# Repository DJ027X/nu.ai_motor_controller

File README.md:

# nu.ai_motor_controller
Designed with KiCAD 5.

You'll also want to grab my custom KiCAD library repo, otherwise parts may not load in.

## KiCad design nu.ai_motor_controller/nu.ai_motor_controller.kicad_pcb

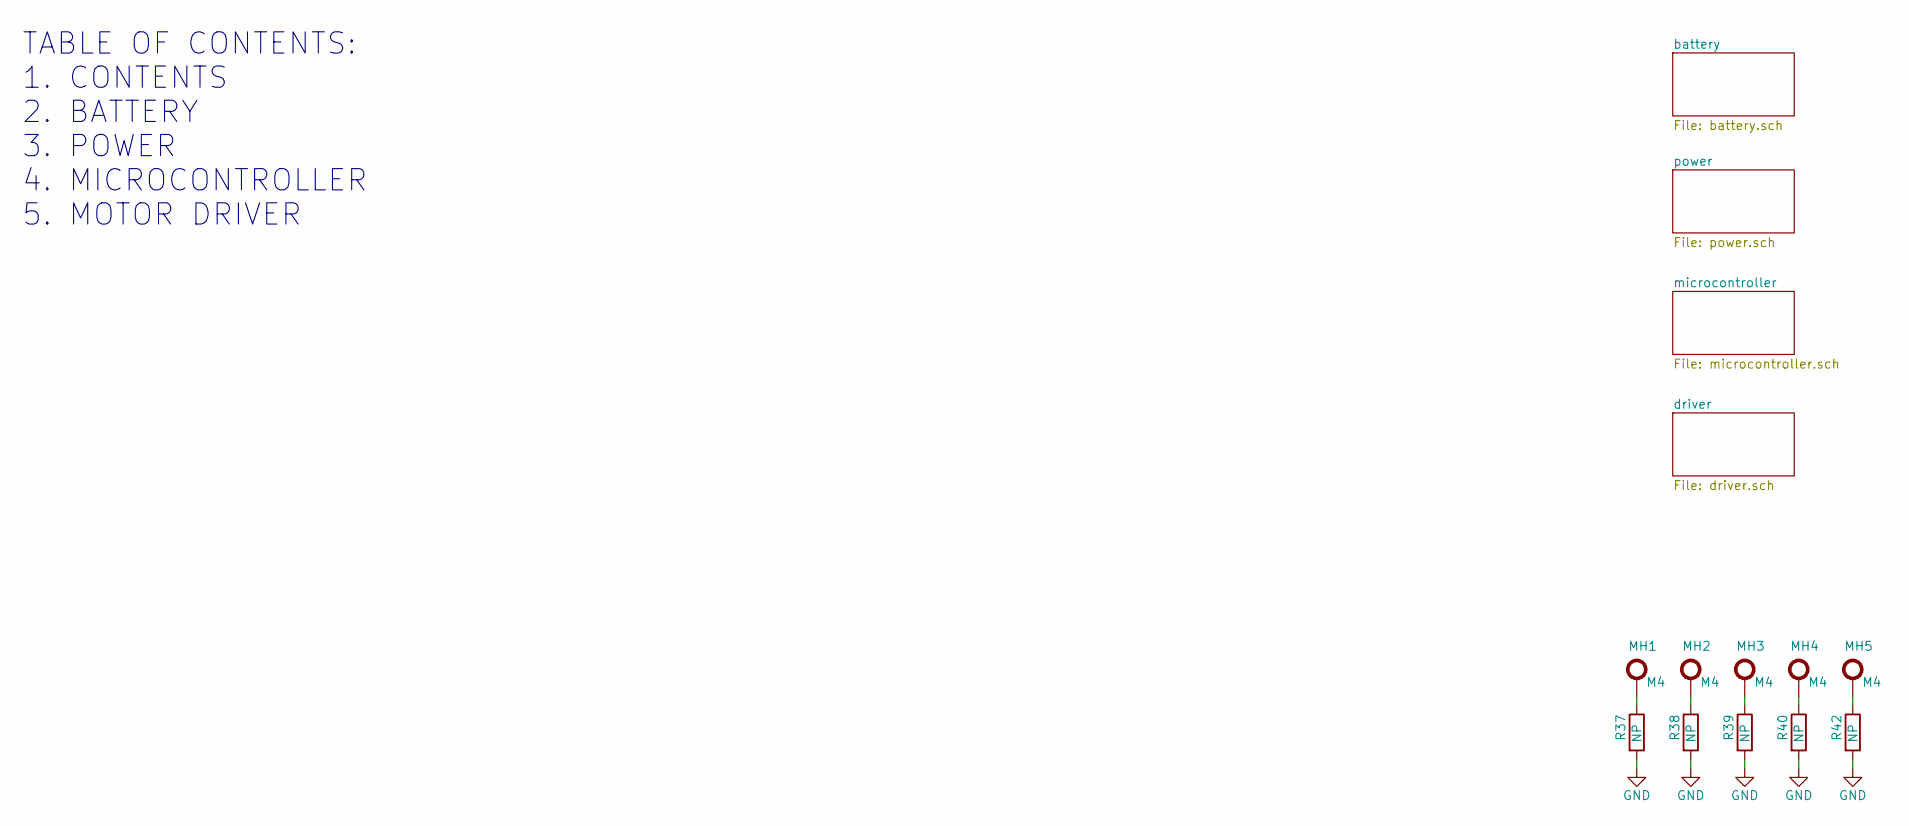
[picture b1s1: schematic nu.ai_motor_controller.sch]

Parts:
MH1, MH2, MH3, MH4, MH5: M4_MOUNTING_HOLE; MountingHole_4.3mm_M4_Pad
R37, R38, R39, R40, R42: NP_R_0603; NP_0603

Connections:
GND: R37.2, R38.2, R39.2, R40.2, R42.2; also elsewhere on the board
unnamed: MH1.1, R37.1
unnamed: MH2.1, R38.1
unnamed: MH3.1, R39.1
unnamed: MH4.1, R40.1
unnamed: MH5.1, R42.1

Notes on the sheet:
TABLE OF CONTENTS: 1. CONTENTS 2. BATTERY 3. POWER 4. MICROCONTROLLER 5. MOTOR DRIVER

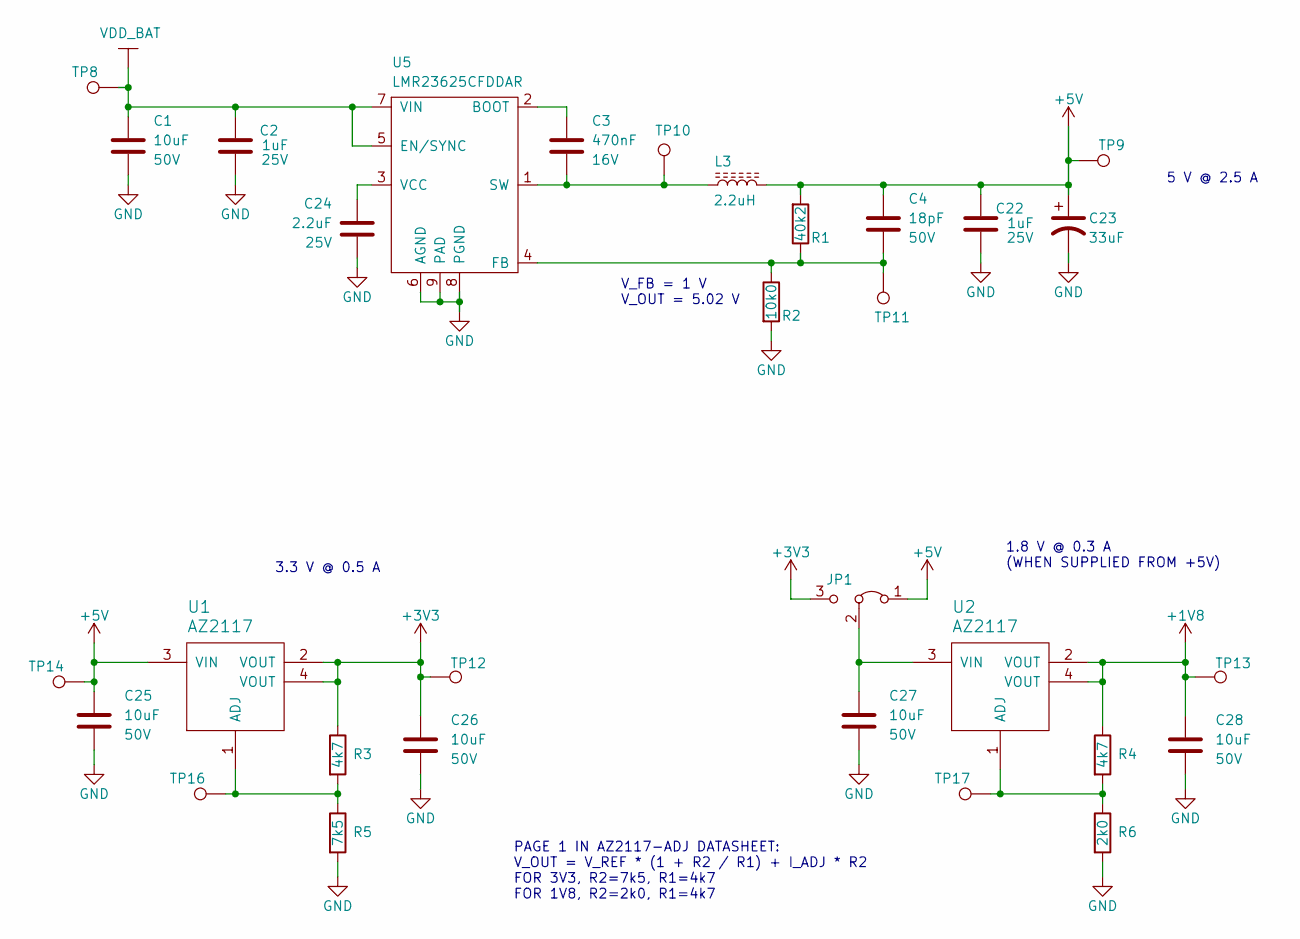
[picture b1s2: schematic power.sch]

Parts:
C1, C25, C26, C27, C28: CL10B103KB8SFNC; C_0603_1608Metric; Rating 50V
C2, C22: CL10B105KA8NNNC; C_0603_1608Metric; Rating 25V
C3: CL10B474KO8NNNC; C_0603_1608Metric; Rating 16V
C4: C0603C180K5RACAUTO; C_0603_1608Metric; Rating 50V
C23: ESH336M035AC3AA; CP_Radial_D5.0mm_P2.00mm
C24: GRM188R61E225KA12D; C_0603_1608Metric; Rating 25V
JP1: Jumper_3_Bridged12; PinHeader_1x03_P2.54mm_Vertical
L3: NR6028T2R2N; L_Taiyo-Yuden_NR-60xx
R1: RMCF0603FT40K2; R_0603_1608Metric
R2: CR0603-JW-103ELF; R_0603_1608Metric
R3, R4: RMCF0603FT4K70; R_0603_1608Metric
R5: RMCF0603FT7K50; R_0603_1608Metric
R6: RMCF0603FT2K00; R_0603_1608Metric
TP8, TP9, TP10, TP11, TP12, TP13, TP14, TP16, TP17: PTH_0.5_mm; TestPoint_THTPad_D1.0mm_Drill0.5mm
U1, U2: AZ2117; SOT-223
U5: LMR23625CFDDAR; 8-PowerSOIC

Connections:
+1V8: C28.1, R4.1, TP13.1, U2.2 (VOUT), U2.4 (VOUT); also elsewhere on the board
+3V3: C26.1, JP1.3 (B), R3.1, TP12.1, U1.2 (VOUT), U1.4 (VOUT); also elsewhere on the board
+5V: C4.1, C22.1, C23.1, C25.1, JP1.1 (A), L3.2, R1.1, TP9.1, TP14.1, U1.3 (VIN); also elsewhere on the board
GND: C1.2, C2.2, C22.2, C23.2, C24.2, C25.2, C26.2, C27.2, C28.2, R2.2, R5.2, R6.2, U5.6 (AGND), U5.8 (PGND), U5.9 (PAD); also elsewhere on the board
unnamed: C3.1, U5.2 (BOOT)
unnamed: C3.2, L3.1, TP10.1, U5.1 (SW)
unnamed: C4.2, R1.2, R2.1, TP11.1, U5.4 (FB)
unnamed: C24.1, U5.3 (VCC)
unnamed: C27.1, JP1.2 (C), U2.3 (VIN)
unnamed: R3.2, R5.1, TP16.1, U1.1 (ADJ)
unnamed: R4.2, R6.1, TP17.1, U2.1 (ADJ)
VDD_BAT: C1.1, C2.1, TP8.1, U5.5 (EN/SYNC), U5.7 (VIN); also elsewhere on the board

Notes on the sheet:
V_FB = 1 V V_OUT = 5.02 V
5 V @ 2.5 A
PAGE 1 IN AZ2117-ADJ DATASHEET: V_OUT = V_REF * (1 + R2 / R1) + I_ADJ * R2 FOR 3V3, R2=7k5, R1=4k7 FOR 1V8, R2=2k0, R1=4k7
3.3 V @ 0.5 A
1.8 V @ 0.3 A (WHEN SUPPLIED FROM +5V)

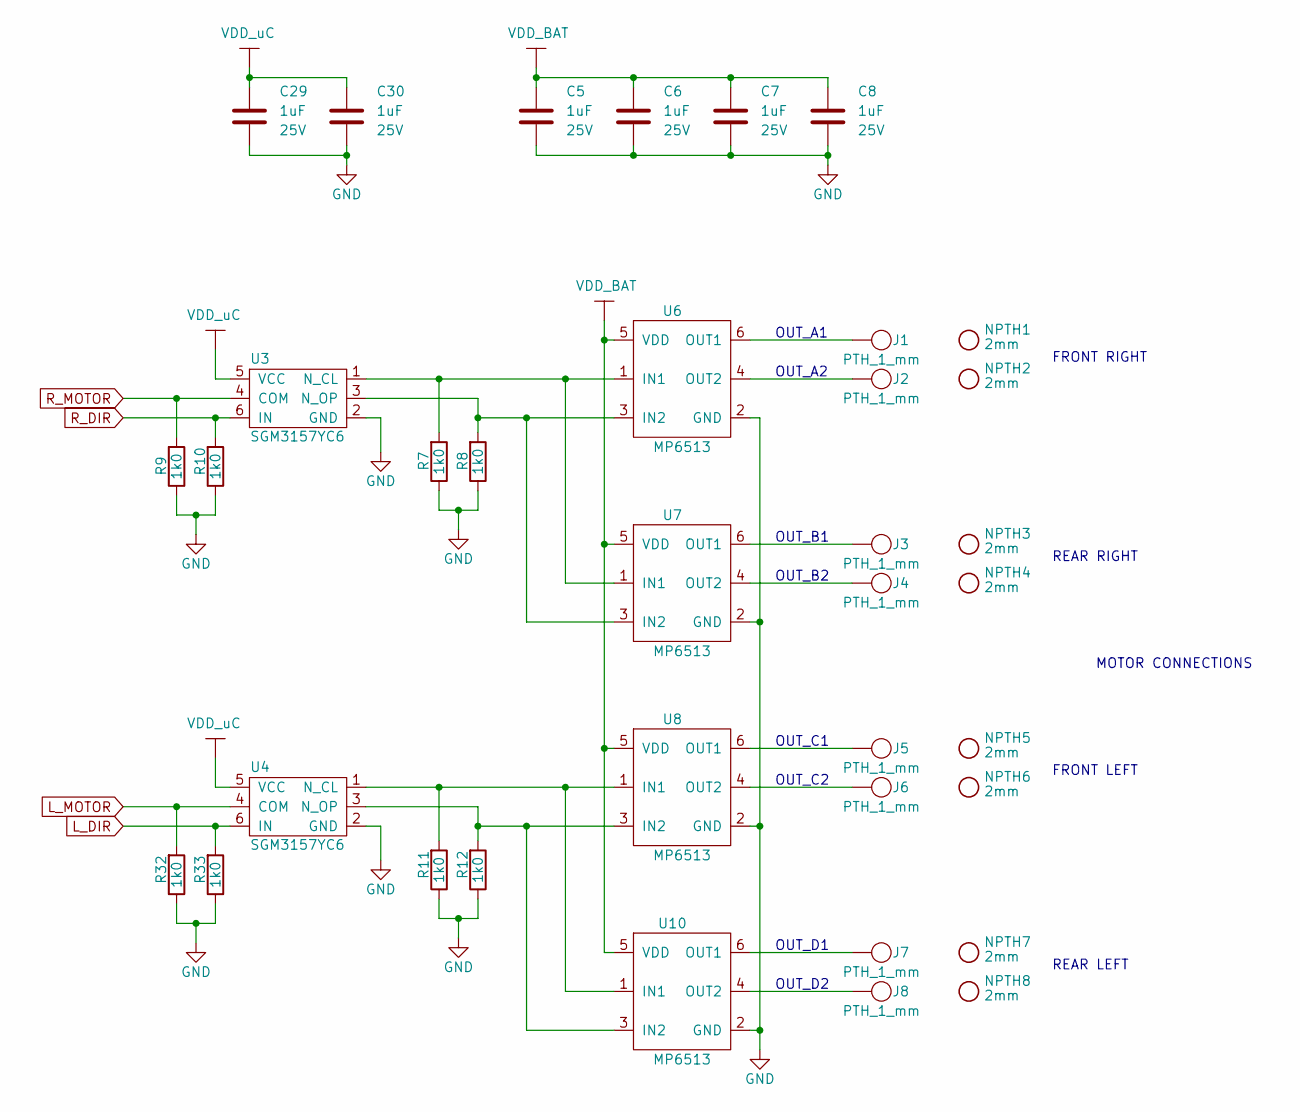
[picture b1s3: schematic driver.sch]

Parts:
C5, C6, C7, C8, C29, C30: CL10B105KA8NNNC; C_0603_1608Metric; Rating 25V
J1, J2, J3, J4, J5, J6, J7, J8: PTH_1_mm; TestPoint_THTPad_D2.0mm_Drill1.0mm
NPTH1, NPTH2, NPTH3, NPTH4, NPTH5, NPTH6, NPTH7, NPTH8: NPTH_2mm
R7, R8, R9, R10, R11, R12, R32, R33: RC0603JR-071KL; R_0603_1608Metric
U3, U4: SGM3157YC6; SOT-363_SC-70-6
U6, U7, U8, U10: MP6513; TSOT23-6

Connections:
GND: C5.2, C6.2, C7.2, C8.2, C29.2, C30.2, R7.2, R8.2, R9.2, R10.2, R11.2, R12.2, R32.2, R33.2, U3.2 (GND), U4.2 (GND), U6.2 (GND), U7.2 (GND), U8.2 (GND), U10.2 (GND); also elsewhere on the board
L_DIR: R33.1, U4.6 (IN); also elsewhere on the board
L_MOTOR: R32.1, U4.4 (COM); also elsewhere on the board
unnamed: J1.1, U6.6 (OUT1)
unnamed: J2.1, U6.4 (OUT2)
unnamed: J3.1, U7.6 (OUT1)
unnamed: J4.1, U7.4 (OUT2)
unnamed: J5.1, U8.6 (OUT1)
unnamed: J6.1, U8.4 (OUT2)
unnamed: J7.1, U10.6 (OUT1)
unnamed: J8.1, U10.4 (OUT2)
unnamed: R7.1, U3.1 (N_CL), U6.1 (IN1), U7.1 (IN1)
unnamed: R8.1, U3.3 (N_OP), U6.3 (IN2), U7.3 (IN2)
unnamed: R11.1, U4.1 (N_CL), U8.1 (IN1), U10.1 (IN1)
unnamed: R12.1, U4.3 (N_OP), U8.3 (IN2), U10.3 (IN2)
R_DIR: R10.1, U3.6 (IN); also elsewhere on the board
R_MOTOR: R9.1, U3.4 (COM); also elsewhere on the board
VDD_BAT: C5.1, C6.1, C7.1, C8.1, U6.5 (VDD), U7.5 (VDD), U8.5 (VDD), U10.5 (VDD); also elsewhere on the board
VDD_uC: C29.1, C30.1, U3.5 (VCC), U4.5 (VCC); also elsewhere on the board

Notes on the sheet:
OUT_A1
OUT_A2
OUT_B1
OUT_B2
OUT_C1
OUT_C2
OUT_D1
OUT_D2
MOTOR CONNECTIONS
FRONT RIGHT
REAR RIGHT
FRONT LEFT
REAR LEFT

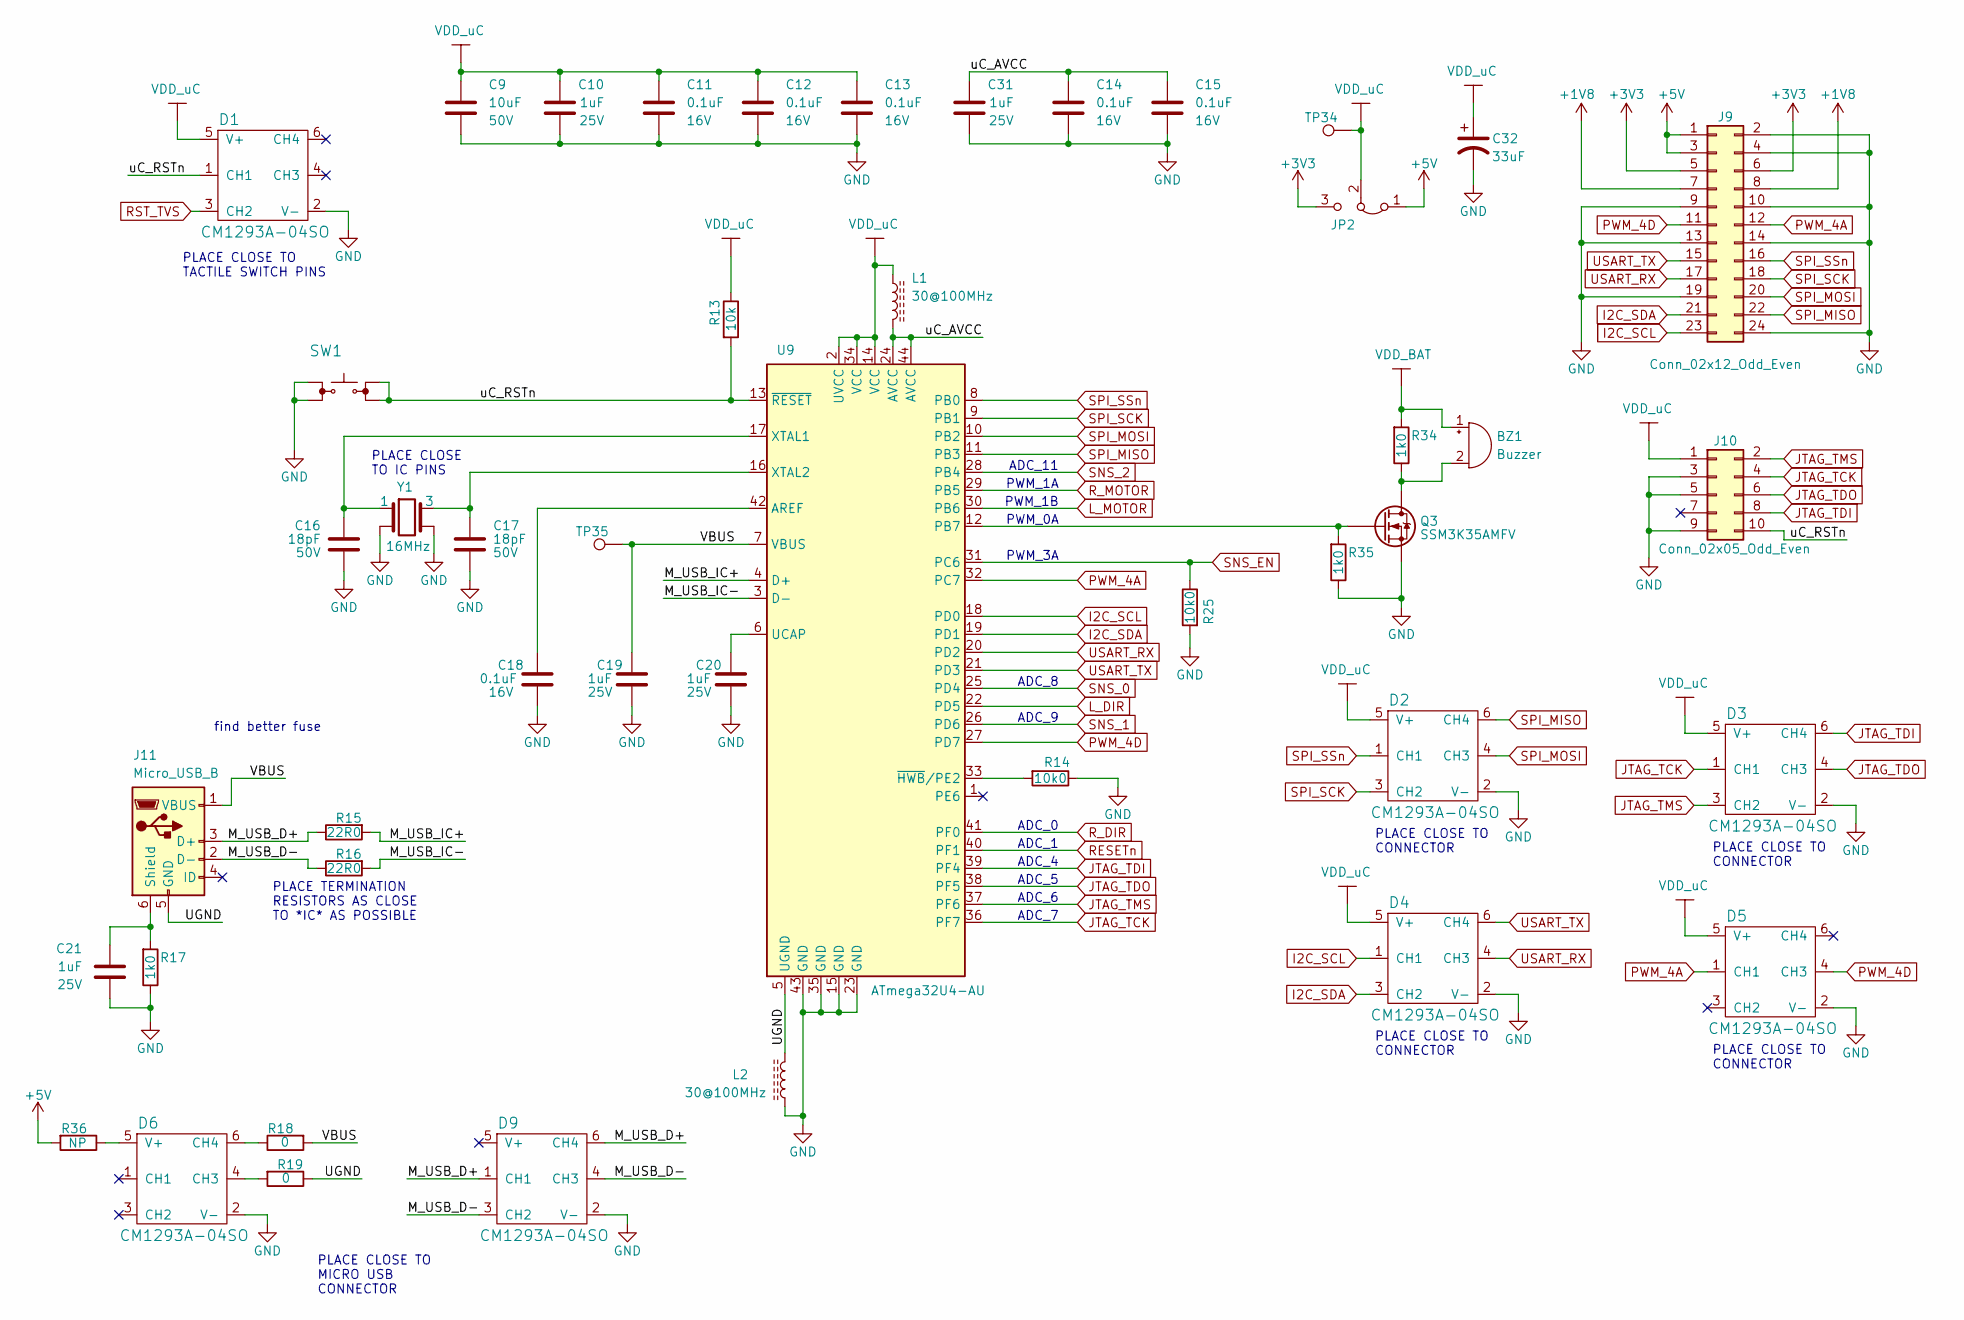
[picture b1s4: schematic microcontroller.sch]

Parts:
BZ1: Buzzer; 0.5_IN_BUZZER
C9: CL10B103KB8SFNC; C_0603_1608Metric; Rating 50V
C10, C19, C20, C21, C31: CL10B105KA8NNNC; C_0603_1608Metric; Rating 25V
C11, C12, C13, C14, C15, C18: CL10B104KO8NNNC; C_0603_1608Metric; Rating 16V
C16, C17: C0603C180K5RACAUTO; C_0603_1608Metric; Rating 50V
C32: ESH336M035AC3AA; CP_Radial_D5.0mm_P2.00mm
D1, D2, D3, D4, D5, D6, D9: CM1293A-04SO; SOT-457
J9: Conn_02x12_Odd_Even; PinHeader_2x12_P2.54mm_Vertical
J10: Conn_02x05_Odd_Even; PinHeader_2x05_P2.54mm_Vertical
J11: DX4R105JJCR1800; DX4R105JJCR1800‎_MICRO_USB_B_CONNECTOR
JP2: Jumper_3_Bridged12; PinHeader_1x03_P2.54mm_Vertical
L1, L2: CIS10P300AC; L_0603_1608Metric
Q3: SSM3K35AMFV; SOT-723
R13, R14, R25: CR0603-JW-103ELF; R_0603_1608Metric
R15, R16: RMCF0603FT22R0; R_0603_1608Metric
R17, R34, R35: RC0603JR-071KL; R_0603_1608Metric
R18, R19: RC0603JR-070RL; R_0603_1608Metric
R36: NP_R_0603; NP_0603
SW1: TACTILE_SWITCH
TP34, TP35: PTH_0.5_mm; TestPoint_THTPad_D1.0mm_Drill0.5mm
U9: ATmega32U4-AU; TQFP-44_10x10mm_P0.8mm
Y1: 7M-16.000MAAE-T; Crystal_SMD_3225-4Pin_3.2x2.5mm

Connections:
+1V8: J9.7, J9.8; also elsewhere on the board
+3V3: J9.5, J9.6, JP2.3 (B); also elsewhere on the board
+5V: J9.1, J9.3, JP2.1 (A), R36.2; also elsewhere on the board
/microcontroller/M_USB_D+: D9.1 (CH1), D9.6 (CH4), J11.3 (D+), R15.2
/microcontroller/M_USB_D-: D9.3 (CH2), D9.4 (CH3), J11.2 (D-), R16.2
/microcontroller/M_USB_IC+: R15.1, U9.4 (D+)
/microcontroller/M_USB_IC-: R16.1, U9.3 (D-)
/microcontroller/UGND: J11.5 (GND), L2.1, R19.1, U9.5 (UGND)
/microcontroller/VBUS: C19.1, J11.1 (VBUS), R18.2, TP35.1, U9.7 (VBUS)
/microcontroller/uC_AVCC: C14.1, C15.1, C31.1, L1.2, U9.24 (AVCC), U9.44 (AVCC)
/microcontroller/uC_RSTn: D1.1 (CH1), J10.10, R13.2, SW1.2, U9.13 (~RESET)
GND: C9.2, C10.2, C11.2, C12.2, C13.2, C14.2, C15.2, C16.2, C17.2, C18.2, C19.2, C20.2, C21.2, C31.2, C32.2, D1.2 (V-), D2.2 (V-), D3.2 (V-), D4.2 (V-), D5.2 (V-), D6.2 (V-), D9.2 (V-), J9.2, J9.4, J9.9, J9.10, J9.13, J9.14, J9.19, J9.24, J10.3, J10.5, J10.9, L2.2, Q3.2 (S), R14.1, R17.2, R25.2, R35.2, SW1.1, U9.15 (GND), U9.23 (GND), U9.35 (GND), U9.43 (GND), Y1.2, Y1.4; also elsewhere on the board
I2C_SCL: D4.1 (CH1), J9.23, U9.18 (PD0)
I2C_SDA: D4.3 (CH2), J9.21, U9.19 (PD1)
JTAG_TCK: D3.1 (CH1), J10.4, U9.36 (PF7)
JTAG_TDI: D3.6 (CH4), J10.8, U9.39 (PF4)
JTAG_TDO: D3.4 (CH3), J10.6, U9.38 (PF5)
JTAG_TMS: D3.3 (CH2), J10.2, U9.37 (PF6)
L_DIR: U9.22 (PD5); also elsewhere on the board
L_MOTOR: U9.30 (PB6); also elsewhere on the board
unnamed: BZ1.2 (+), Q3.3 (D), R34.2
unnamed: C16.1, U9.17 (XTAL1), Y1.1
unnamed: C17.1, U9.16 (XTAL2), Y1.3
unnamed: C18.1, U9.42 (AREF)
unnamed: C20.1, U9.6 (UCAP)
unnamed: C21.1, J11.6 (Shield), R17.1
unnamed: D6.4 (CH3), R19.2
unnamed: D6.5 (V+), R36.1
unnamed: D6.6 (CH4), R18.1
unnamed: Q3.1 (G), R35.1, U9.12 (PB7)
unnamed: R14.2, U9.33 (~HWB~/PE2)
PWM_4A: D5.1 (CH1), J9.12, U9.32 (PC7)
PWM_4D: D5.4 (CH3), J9.11, U9.27 (PD7)
RESETn: U9.40 (PF1); also elsewhere on the board
RST_TVS: D1.3 (CH2); also elsewhere on the board
R_DIR: U9.41 (PF0); also elsewhere on the board
R_MOTOR: U9.29 (PB5); also elsewhere on the board
SNS_0: U9.25 (PD4); also elsewhere on the board
SNS_1: U9.26 (PD6); also elsewhere on the board
SNS_2: U9.28 (PB4); also elsewhere on the board
SNS_EN: R25.1, U9.31 (PC6); also elsewhere on the board
SPI_MISO: D2.6 (CH4), J9.22, U9.11 (PB3)
SPI_MOSI: D2.4 (CH3), J9.20, U9.10 (PB2)
SPI_SCK: D2.3 (CH2), J9.18, U9.9 (PB1)
SPI_SSn: D2.1 (CH1), J9.16, U9.8 (PB0)
USART_RX: D4.4 (CH3), J9.17, U9.20 (PD2)
USART_TX: D4.6 (CH4), J9.15, U9.21 (PD3)
VDD_BAT: BZ1.1 (-), R34.1; also elsewhere on the board
VDD_uC: C9.1, C10.1, C11.1, C12.1, C13.1, C32.1, D1.5 (V+), D2.5 (V+), D3.5 (V+), D4.5 (V+), D5.5 (V+), J10.1, JP2.2 (C), L1.1, R13.1, TP34.1, U9.2 (UVCC), U9.14 (VCC), U9.34 (VCC); also elsewhere on the board

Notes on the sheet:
PLACE TERMINATION RESISTORS AS CLOSE TO *IC* AS POSSIBLE
PLACE CLOSE TO MICRO USB CONNECTOR
PLACE CLOSE TO IC PINS
ADC_11
PWM_1A
PWM_1B
ADC_8
ADC_9
ADC_0
ADC_1
ADC_4
ADC_5
ADC_6
ADC_7
PLACE CLOSE TO TACTILE SWITCH PINS
PWM_0A
PLACE CLOSE TO CONNECTOR
find better fuse
PWM_3A

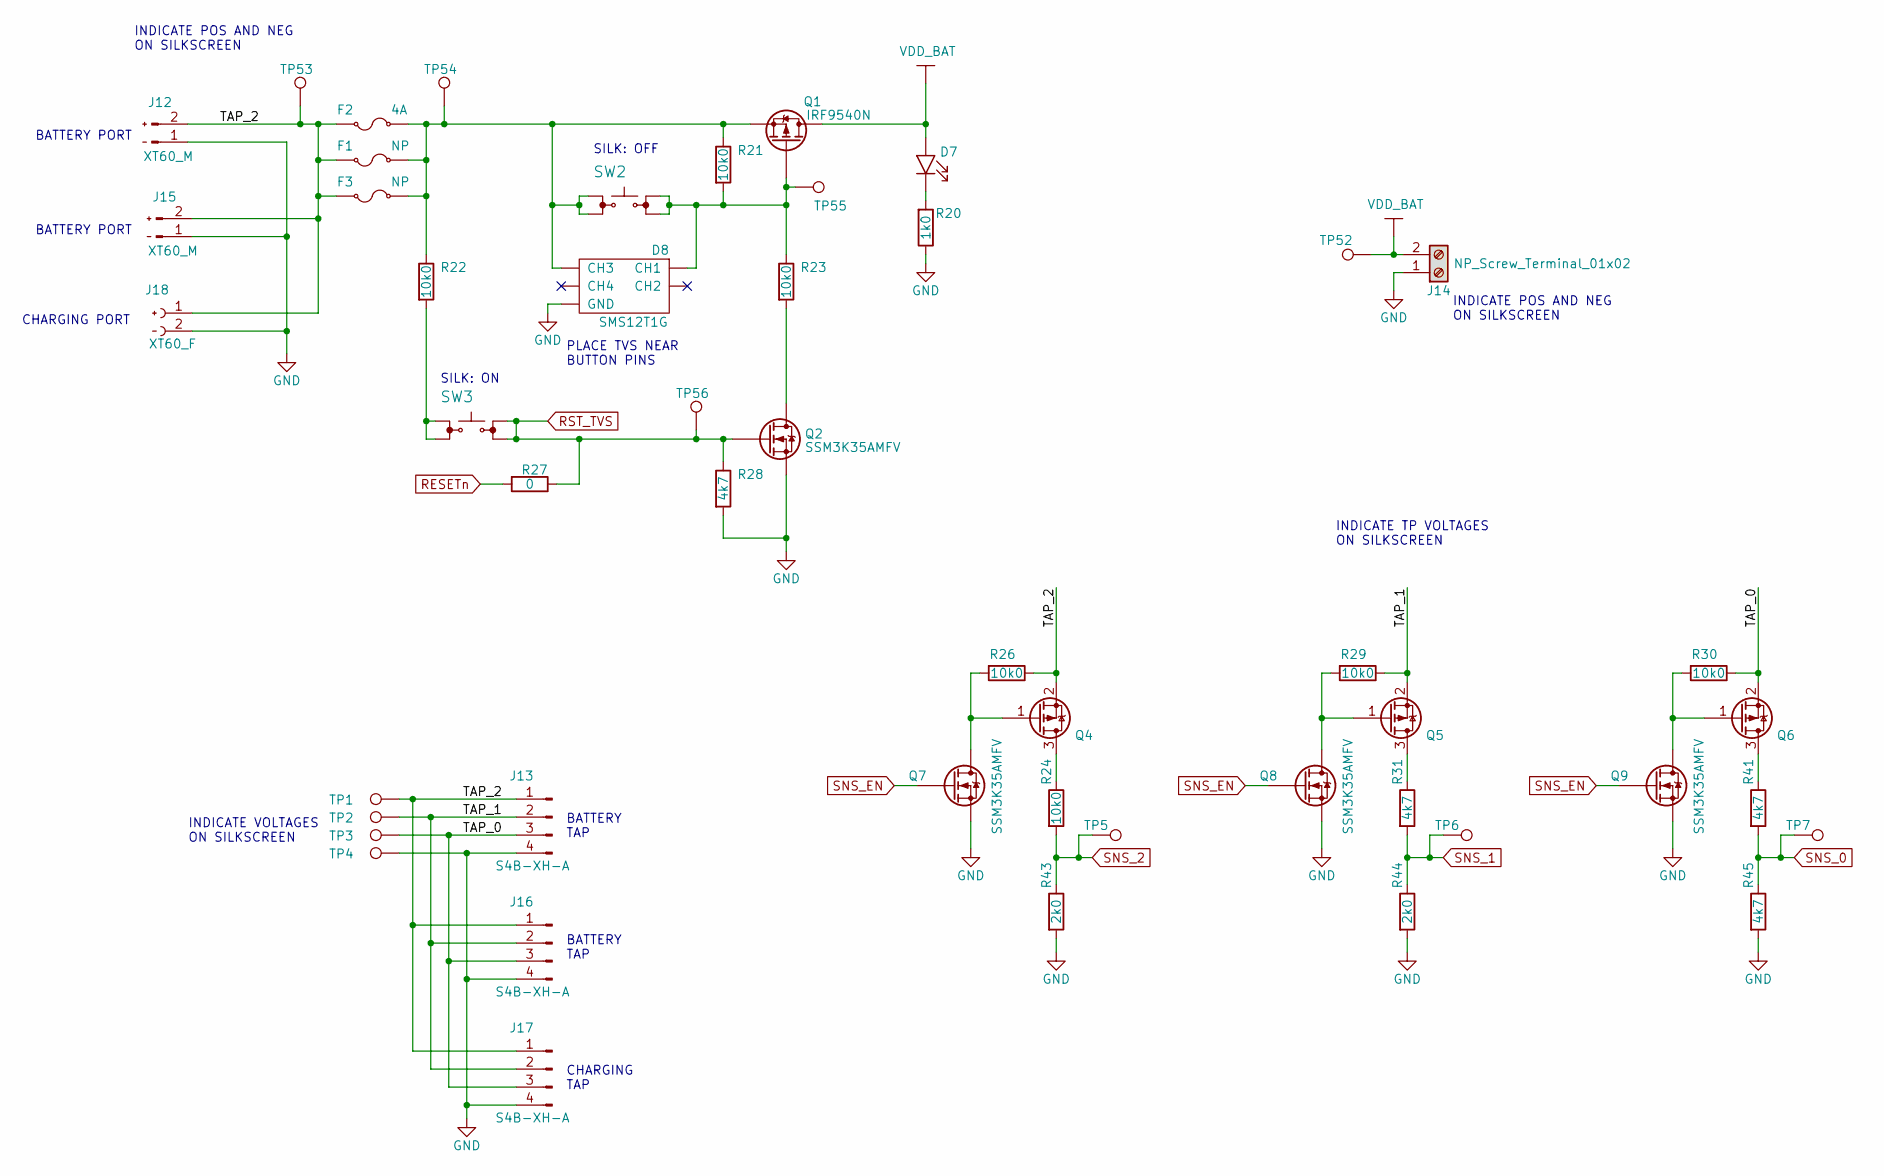
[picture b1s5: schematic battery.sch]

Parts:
D7: LED_GENERIC_0805; D_0805_2012Metric
D8: SMS12T1G; SOT-457
F1, F3: NP_FUSE_0603; Fuse_0603_1608Metric
F2: ERB-RE4R00V; Fuse_0603_1608Metric; rating 4A
J12, J15: XT60_RA_MALE; XT60PW
J13, J16, J17: S4B-XH-A; X4B-XH-A
J14: NP_Screw_Terminal_01x02; TERMINAL_BLOCK_1x2
J18: XT60_RA_FEMALE; XT60PW
Q1: IRF9540N; TO-220-3_Horizontal_TabDown
Q2, Q7, Q8, Q9: SSM3K35AMFV; SOT-723
Q4, Q5, Q6: AO3407A; SOT-23
R20: RC0603JR-071KL; R_0603_1608Metric
R21, R22, R23, R24, R26, R29, R30: CR0603-JW-103ELF; R_0603_1608Metric
R27: RC0603JR-070RL; R_0603_1608Metric
R28, R31, R41, R45: RMCF0603FT4K70; R_0603_1608Metric
R43, R44: RMCF0603FT2K00; R_0603_1608Metric
SW2, SW3: TACTILE_SWITCH
TP1, TP2, TP3, TP4, TP5, TP6, TP7, TP52, TP53, TP54, TP55, TP56: PTH_0.5_mm; TestPoint_THTPad_D1.0mm_Drill0.5mm

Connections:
/battery/TAP_0: J13.3, J16.3, J17.3, Q6.2 (S), R30.1, TP3.1
/battery/TAP_1: J13.2, J16.2, J17.2, Q5.2 (S), R29.1, TP2.1
/battery/TAP_2: F1.1, F2.1, F3.1, J12.2, J13.1, J15.2, J16.1, J17.1, J18.1, Q4.2 (S), R26.1, TP1.1, TP53.1
GND: D8.2 (GND), D8.5 (GND), J12.1, J13.4, J14.1, J15.1, J16.4, J17.4, J18.2, Q2.2 (S), Q7.2 (S), Q8.2 (S), Q9.2 (S), R20.2, R28.2, R43.2, R44.2, R45.2, TP4.1; also elsewhere on the board
unnamed: D7.1 (K), R20.1
unnamed: D8.1 (CH1), Q1.1 (G), R21.2, R23.1, SW2.2, TP55.1
unnamed: D8.6 (CH3), F1.2, F2.2, F3.2, Q1.3 (S), R21.1, R22.1, SW2.1, TP54.1
unnamed: Q2.3 (D), R23.2
unnamed: Q4.1 (G), Q7.3 (D), R26.2
unnamed: Q4.3 (D), R24.1
unnamed: Q5.1 (G), Q8.3 (D), R29.2
unnamed: Q5.3 (D), R31.1
unnamed: Q6.1 (G), Q9.3 (D), R30.2
unnamed: Q6.3 (D), R41.1
unnamed: R22.2, SW3.1
RESETn: R27.2; also elsewhere on the board
RST_TVS: Q2.1 (G), R27.1, R28.1, SW3.2, TP56.1; also elsewhere on the board
SNS_0: R41.2, R45.1, TP7.1; also elsewhere on the board
SNS_1: R31.2, R44.1, TP6.1; also elsewhere on the board
SNS_2: R24.2, R43.1, TP5.1; also elsewhere on the board
SNS_EN: Q7.1 (G), Q8.1 (G), Q9.1 (G); also elsewhere on the board
VDD_BAT: D7.2 (A), J14.2, Q1.2 (D), Q1.4 (D), TP52.1; also elsewhere on the board

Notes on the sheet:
BATTERY TAP
INDICATE POS AND NEG ON SILKSCREEN
INDICATE VOLTAGES ON SILKSCREEN
PLACE TVS NEAR BUTTON PINS
SILK: OFF
SILK: ON
BATTERY PORT
CHARGING PORT
CHARGING TAP
INDICATE TP VOLTAGES ON SILKSCREEN

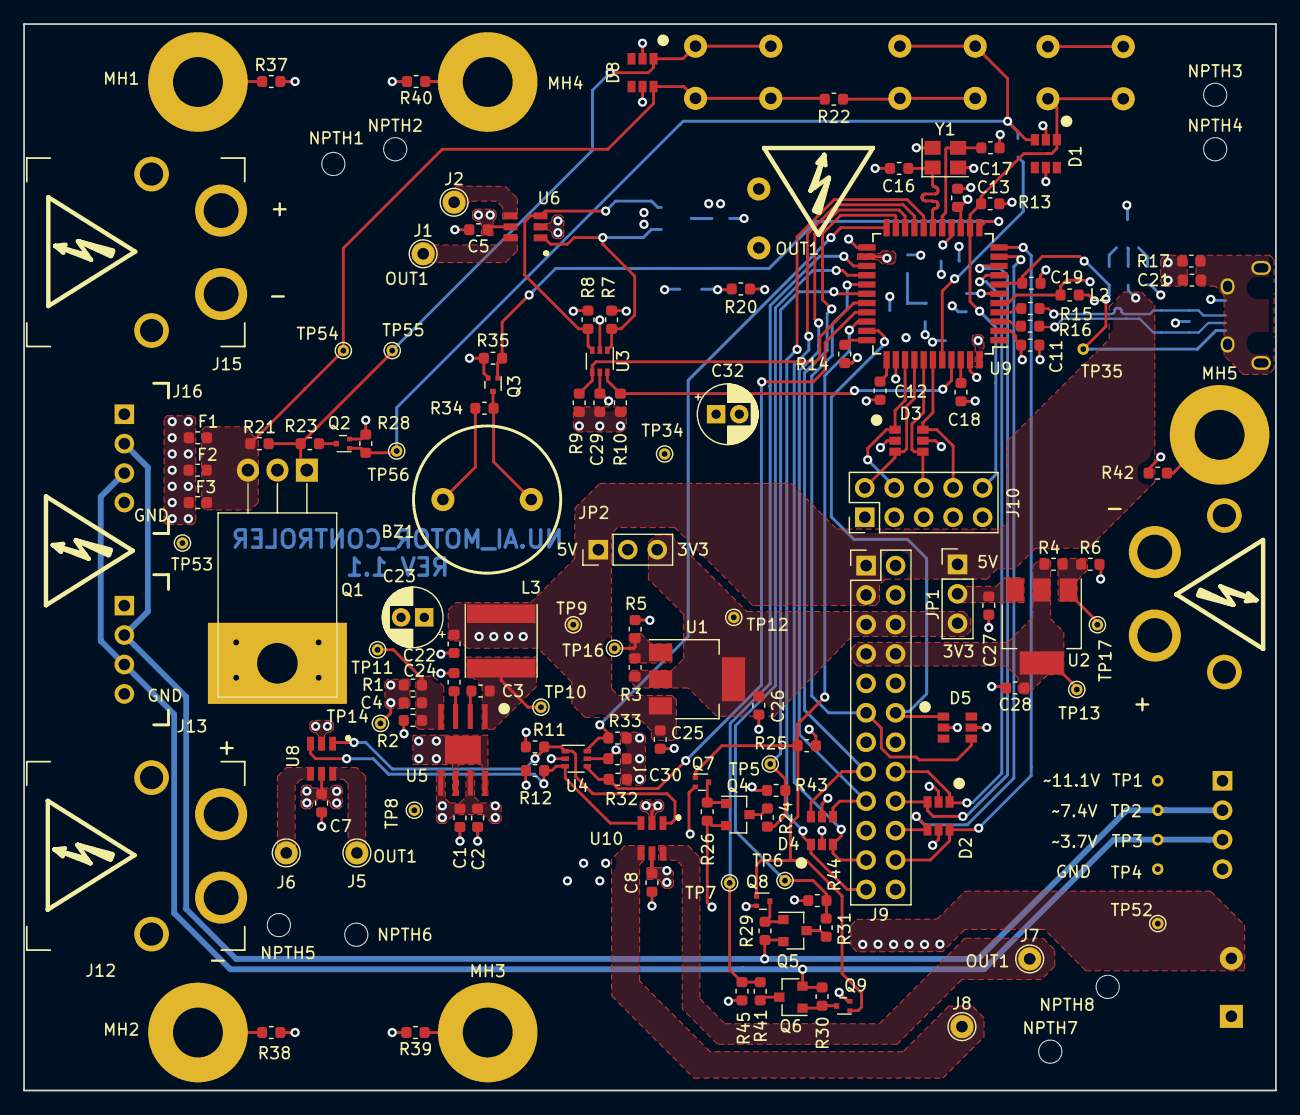
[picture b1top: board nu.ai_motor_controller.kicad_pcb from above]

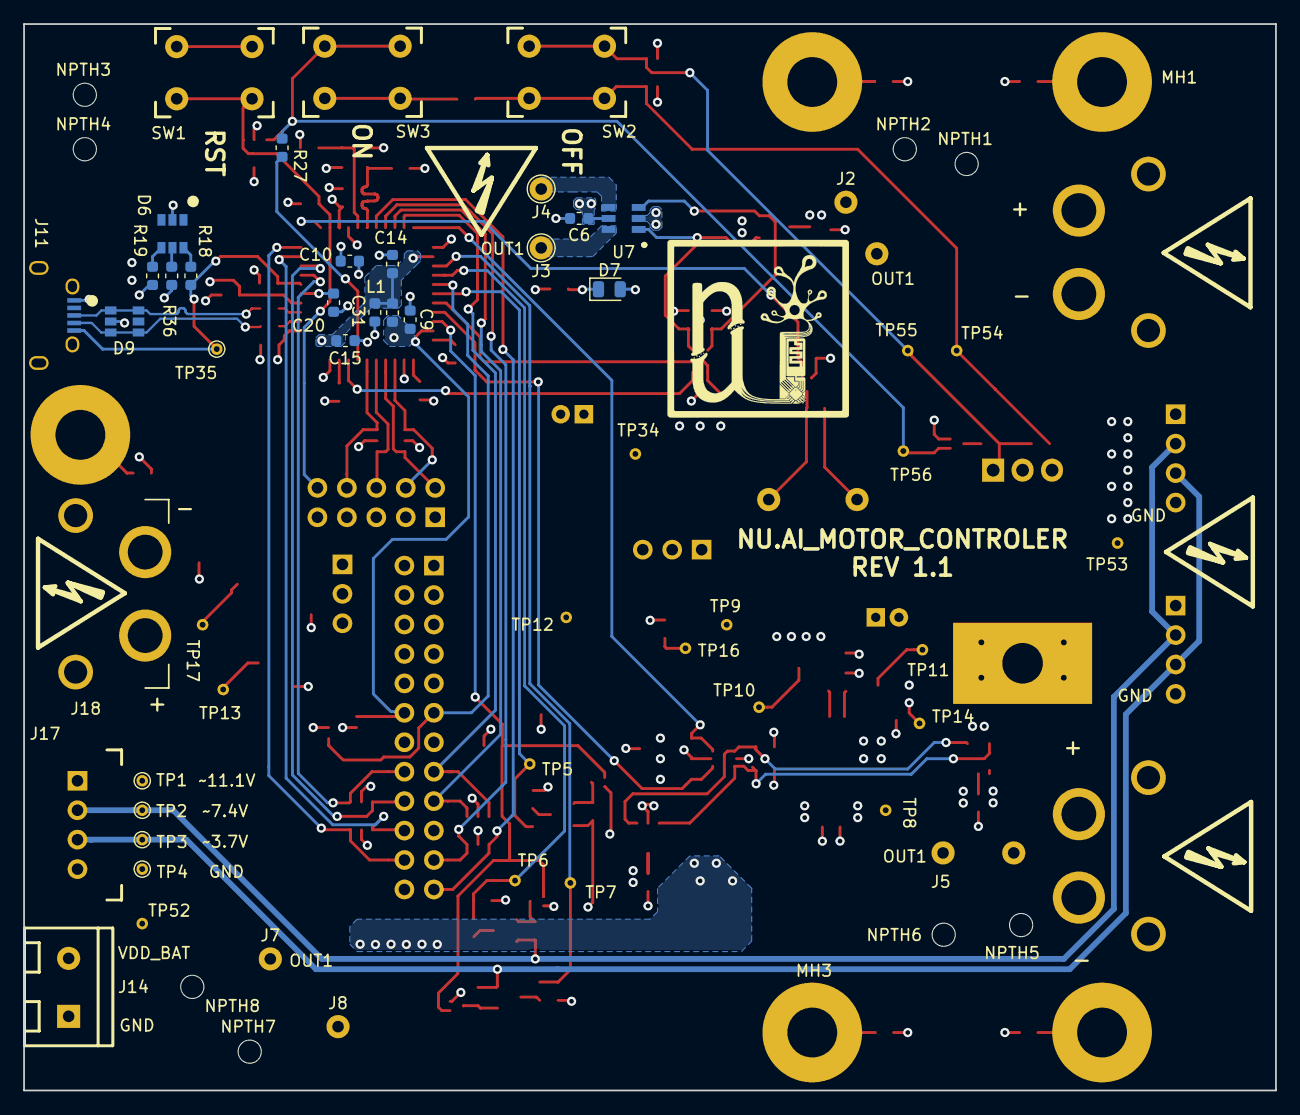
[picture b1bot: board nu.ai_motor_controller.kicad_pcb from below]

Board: 4 copper layers, 108.0 x 92.0 mm, 172 parts (30 on the bottom side), 87 nets.

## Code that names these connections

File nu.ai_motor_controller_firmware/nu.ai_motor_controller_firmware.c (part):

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
// Just some pin name mapping for your own reference
/*
PIN8  PORTB0 SPI_SSn
PIN9  PORTB1 SPI_SCK
PIN10 PORTB2 SPI_MOSI
PIN11 PORTB3 SPI_MISO
PIN28 PORTB4 SNS_2
PIN29 PORTB5 R_MOTOR
PIN30 PORTB6 L_MOTOR
PIN12 PORTB7 BUZZER
PIN31 PORTC6 SNS_EN
PIN32 PORTC7 PWM_4A
PIN18 PORTD0 I2C_SCL
PIN19 PORTD1 I2C_SDA
PIN20 PORTD2 USART_RX
PIN21 PORTD3 USART_TX
PIN25 PORTD4 SNS_0
PIN22 PORTD5 L_DIR
PIN26 PORTD6 SNS_1
PIN27 PORTD7 PWM_4D
PIN33 PORTE2 HWBn
PIN1  PORTE6 NC
PIN41 PORTF0 R_DIR
PIN40 PORTF1 RESETn
PIN39 PORTF4 JTAG_TDI
PIN38 PORTF5 JTAG_TDO
PIN37 PORTF6 JTAG_TMS
PIN36 PORTF7 JTAG_TCK
*/

// Some handy defines
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
	/*TODO: maybe set ADTS and ADATE to make conversion happen periodically. This is a power saving measure.\
	      if there aren't enough timers, just leave in free-running mode.\
	      Note however that there's a SNS_EN pin that should take care of power saving\
	      so it's probably fine free-running the ADCs.

	TODO: remember later on to make code to switch which ADC port is being read by changing MUX5..0*/
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	// Set prescalar to 256 (~122 Hz to  31250 Hz)
	TCCR0B |= 0x04;

	// Set PB7 as an output to turn the beeping on.
	// Set as input to turn off beeping.
	

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	// Set prescalar to 1024.
	TCCR3B |= 0x05;

	// Set the SNS_EN pin as an output.
	DDRC |= SNS_EN_MASK;

	// Unmask (allow) the interrupt.
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	// This is to prevent a false startup due to back EMF from the motors.
	_delay_ms(2000);

	// Set the RESETn pin as an output.
	DDRF |= (1 << RESETn_OFFSET);
	
	// Set the RESETn pin high. This will keep the board powered on until
	// a user presses the off button, or this pin goes low or high-z.
	// This allows the system to turn itself off in the case of LiPo undervoltage.
	PORTF |= (1 << RESETn_OFFSET);
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
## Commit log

2018-12-23 original commit
2019-01-08 Added block diagram, and added some components to the schematic that will end up being removed :/
2019-01-08 minor updates to diagram
2019-01-14 Updated block diagram
2019-01-15 Added voltage sense lines to diagram, and selected atmega32u4 as uC. The 32u4 doesn't require an FT usb/serial converter
2019-01-16 added microcontroller sheet
2019-01-16 fixed file name for project
2019-01-17 cleaned up and renamed project files. Changed custom library management scheme. It now resides in my homedir as a seperate git project, and is pointed to in kicad's symbol library manager
2019-01-17 Added termination resistors
2019-01-18 automated commit
